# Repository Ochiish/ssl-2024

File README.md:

# 2024 season Ri-one SSL circuit
# Content
- MainBoard
- SubBoard
- raspberry pi shield
- phototransistor
- bldc

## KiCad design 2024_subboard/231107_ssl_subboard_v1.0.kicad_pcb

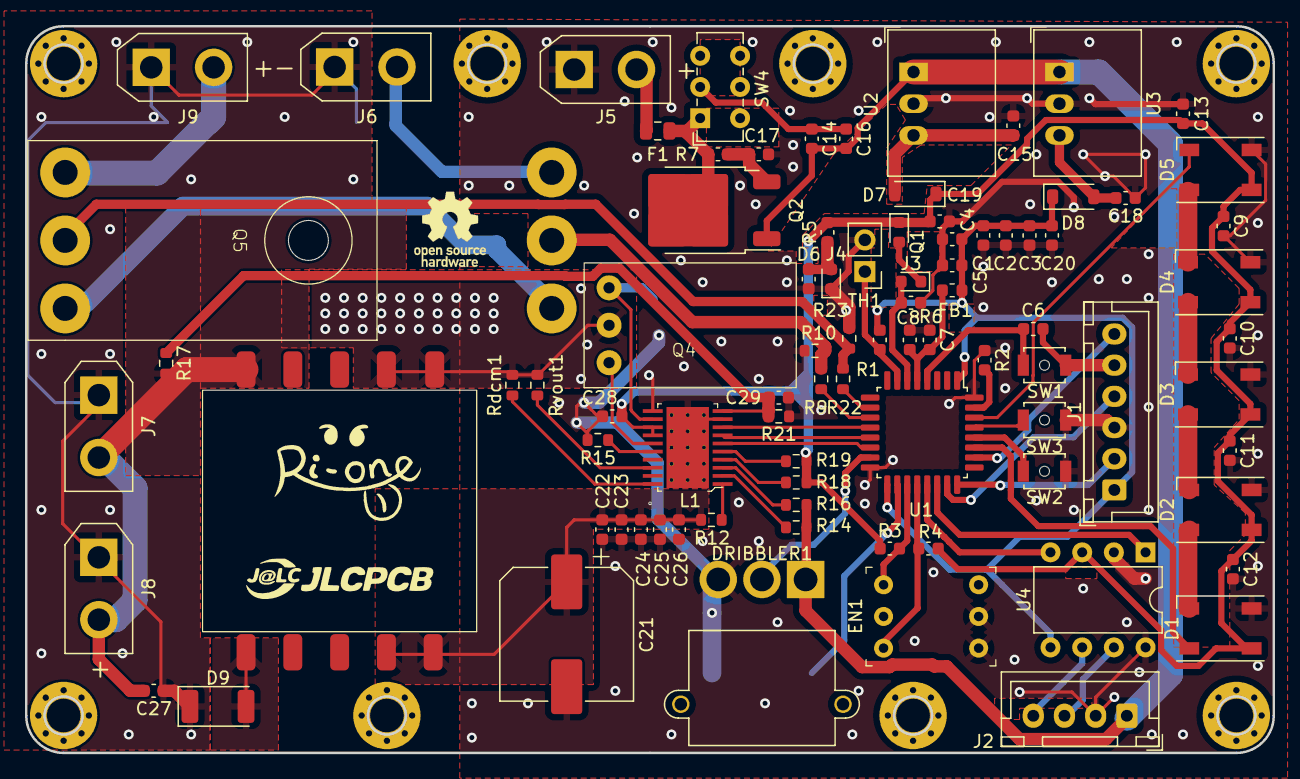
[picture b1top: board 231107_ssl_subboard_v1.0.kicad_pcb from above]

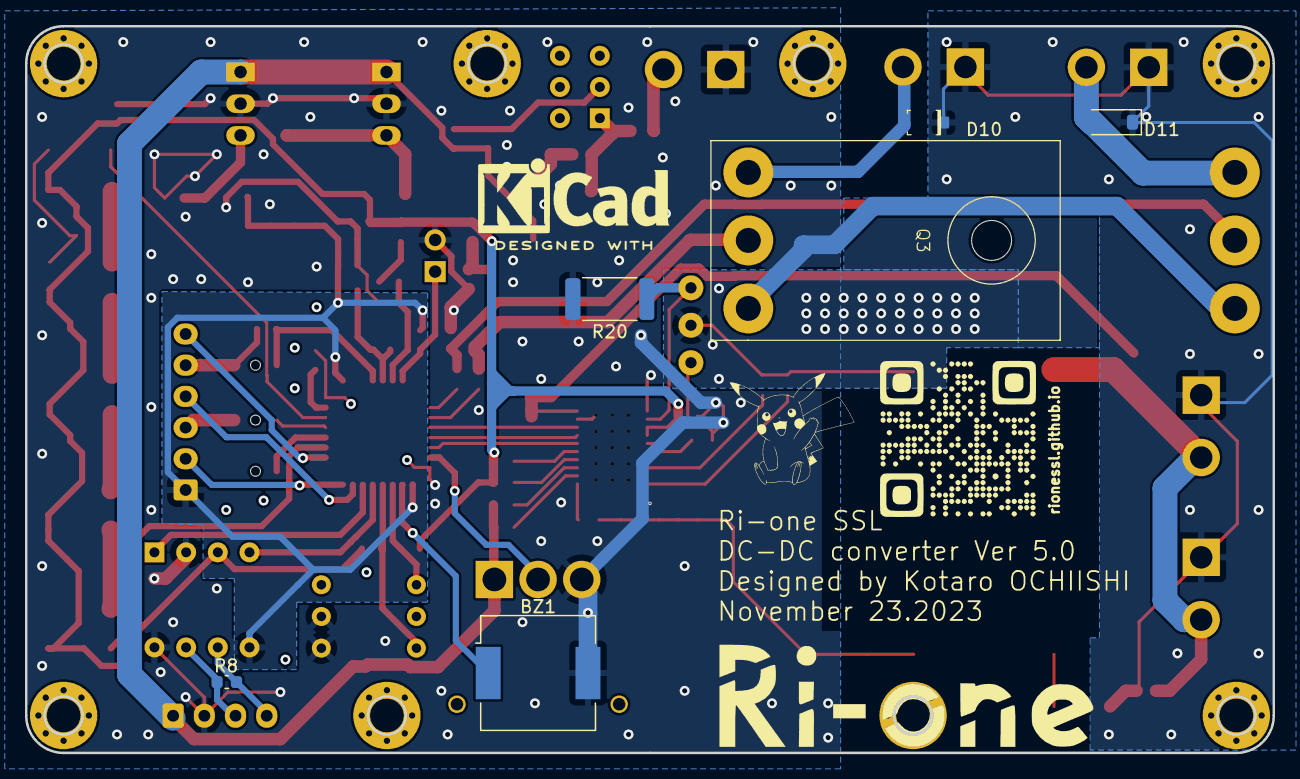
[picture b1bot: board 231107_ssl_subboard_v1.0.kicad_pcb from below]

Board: 2 copper layers, 100.0 x 58.2 mm, 93 parts (6 on the bottom side), 62 nets.

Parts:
BZ1: Buzzer; Buzzer_CUI_CPT-9019S-SMT
C1, C2, C3, C4, C5, C6, C7, C8, C9, C10, C11, C12, C13, C14, C16, C17, C19, C20: 0.1uF; C_0603_1608Metric
C15, C18, C22, C23, C24, C25, C26: 2.2u; C_0603_1608Metric
C21: 680u; CP_Elec_10x10.5
C27: 0.47u; C_0603_1608Metric
C28, C29: 10n; C_0603_1608Metric
D1, D2, D3, D4, D5: ws2812b; LED_Cree-PLCC4_5x5mm_CW
D6: LED; C_0603_1608Metric
D7, D8: SS2040FL; D_SOD-123
D9: 1.5KExxA; D_2010_5025Metric
D10: 1.5KExxA; SOD-123
D11: 1.5KExxA; D_SOD-123
DRIBBLER1: MR30PW-M; AMASS_MR30PW-M_1x03_P3.50mm_Horizontal
EN1: RotaryEncoder_Switch; SOCKET_DIP-6_7.62mm_Conn
F1: Fuse; Fuse_0805_2012Metric
FB1: FerriteBead_Small; L_0603_1608Metric
J1: pc to stm32; JST_XH_B6B-XH-A_1x06_P2.50mm_Vertical
J2: main to sub; JST_XH_B4B-XH-A_1x04_P2.50mm_Vertical
J3: PHOTOCOUPLER; LED_0603_1608Metric
J4: LED; LED_0603_1608Metric
J5: lipo_3cell; AMASS_XT30UPB-M_1x02_P5.0mm_Vertical
J6: s1; AMASS_XT30UPB-F_1x02_P5.0mm_Vertical
J7: c1; AMASS_XT30UPB-F_1x02_P5.0mm_Vertical
J8: c2; AMASS_XT30UPB-F_1x02_P5.0mm_Vertical
J9: s2; AMASS_XT30UPB-F_1x02_P5.0mm_Vertical
L1: TSSOP-20-1EP_W4.4mm
Q1: Q_Photo_NPN; LED_0603_1608Metric
Q2: PMOS; TO-252-2
Q3, Q5: NMOS; IRFP150NPbF
Q4: Q_NMOS_DGS; tk20a60u
R1, R3, R4: 5k; C_0603_1608Metric
R2, R7: 10k; C_0603_1608Metric
R5: 470; C_0603_1608Metric
R6: 20k; C_0603_1608Metric
R8: 120; C_0603_1608Metric
R9, R22: 100; R_0603_1608Metric
R10, R23: 1k; R_0603_1608Metric
R12: 40.2k; R_0603_1608Metric
R14, R18: 69.8k; R_0603_1608Metric
R15: 1.65; R_0603_1608Metric
R16, R19: 475k; R_0603_1608Metric
R17: 124; R_0603_1608Metric
R20: 6m; R_2512_6332Metric
R21: 0.768k; R_0603_1608Metric
Rdcm1: 18.2k; R_0603_1608Metric
Rvout1: 40.2k; R_0603_1608Metric
SW1, SW2, SW3: SW_Push; SW_SPST_B3U-1000P-B
SW4: SW_SPST; SW_E-Switch_EG1271_SPDT
TH1: Thermistor; PinHeader_1x02_P2.54mm_Vertical
U1: STM32F303K8Tx; LQFP-32_7x7mm_P0.8mm
U2: M78AR05-1; Converter_DCDC_RECOM_R-78E-0.5_THT
U3: M78AR033-1; Converter_DCDC_RECOM_R-78E-0.5_THT
U4: MCP2562-E-P; DIP-8_W7.62mm
U5: 32052

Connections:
+3V3: C1.2, C2.2, C3.2, C4.2, C5.2, C20.2, D8.1 (K), FB1.1, J1.1, R1.2, U1.1 (VDD), U1.17 (VDD), U4.5 (Vio)
+5V: C9.1, C10.1, C11.1, C12.1, C13.1, C19.2, C28.1, D1.3 (VDD), D2.3 (VDD), D3.3 (VDD), D4.3 (VDD), D5.3 (VDD), D7.1 (K), L1.13 (VCC), L1.14 (LVGATE), Q1.1 (C), R3.1, R4.1, R5.2, R18.1, R19.1, U4.3 (VDD)
+15V: C14.2, C16.2, DRIBBLER1.1, J2.1, Q2.1 (D), R14.1, R16.1, U2.1 (IN), U3.1 (IN)
+BATT: F1.1, J5.2
CANH: J2.3, R8.2, U4.7 (CANH)
CANL: J2.4, R8.1, U4.6 (CANL)
CANRX: U1.21 (PA11), U4.4 (RXD)
CANTX: U1.22 (PA12), U4.1 (TXD)
CHARGE: L1.8 (CHARGE), U1.12 (PA6)
Cvtrans: C21.1, C22.1, C23.1, C24.1, C25.1, C26.1, R12.1, U5.4 (4IN), U5.5 (5IN)
DCDC_OUT: C27.1, D9.1 (A1), D10.1 (A1), D11.1 (A1), J6.1, J7.1, J8.1, J9.1
DIN: D1.4 (DIN), U1.27 (PB4)
DONE: L1.7 (DONE), U1.13 (PA7)
DOUT: D5.1 (DOUT), U1.30 (PB7)
DR_PWM: DRIBBLER1.2, U1.15 (PB1)
DR_SW: SW3.2, U1.29 (PB6)
Drain: Q4.1 (D), Rdcm1.2, Rvout1.2, U5.6 (6IN), U5.7 (7IN)
ENCODER_A: EN1.1 (A), R3.2, U1.19 (PA9)
ENCODER_B: EN1.3 (B), R4.2, U1.20 (PA10)
FAULT: L1.6 (FAULT), U1.14 (PB0)
GND: BZ1.2 (+), C1.1, C2.1, C3.1, C4.1, C5.1, C7.1, C8.1, C9.2, C10.2, C11.2, C12.2, C13.2, C15.1, C17.1, C18.1, C19.1, C20.1, C21.2, C22.2, C23.2, C24.2, C25.2, C26.2, C28.2, C29.2, D1.2 (GND), D2.2 (GND), D3.2 (GND), D4.2 (GND), D5.2 (GND), D6.1 (K), DRIBBLER1.3, EN1.4 (S1), EN1.5 (S2), J1.3, J2.2, J4.1, J5.1, L1.9 (CLAMP), L1.11 (CSN), L1.21 (GND), Q3.3 (S), Q5.3 (S), R2.1, R6.2, R10.1, R15.2, R20.2, R21.1, R23.1, SW2.1, SW3.1, TH1.2, U1.16 (VSS), U1.32 (VSS), U2.2 (GND), U3.2 (GND), U4.2 (VSS), U4.8 (STBY)
KICK_SW: SW2.2, U1.28 (PB5)
NRST: C6.1, J1.5, SW1.1
unnamed: BZ1.1 (-), U1.18 (PA8)
unnamed: D1.1 (DOUT), D2.4 (DIN)
unnamed: D2.1 (DOUT), D3.4 (DIN)
unnamed: D3.1 (DOUT), D4.4 (DIN)
unnamed: D4.1 (DOUT), D5.4 (DIN)
unnamed: D6.2 (A), J4.2, R5.1
unnamed: C15.2, D7.2 (A), U2.3 (OUT)
unnamed: C18.2, D8.2 (A), U3.3 (OUT)
unnamed: D10.2 (A2), J6.2, Q3.1 (D)
unnamed: D11.2 (A2), J9.2, Q5.1 (D)
unnamed: J3.1, Q1.2 (E)
unnamed: L1.12 (CSP), Q4.3 (S), R20.1
unnamed: C29.1, L1.10 (FB), R17.1, R21.2
unnamed: L1.15 (HVGATE), Q4.2 (G)
unnamed: L1.3 (OVLO1), R16.2
unnamed: L1.5 (OVLO2), R19.2
unnamed: L1.16 (RBG), R15.1
unnamed: L1.20 (RDCM), Rdcm1.1
unnamed: L1.18 (RVOUT), Rvout1.1
unnamed: L1.1 (RVTRANS), R12.2
unnamed: L1.2 (UVLO1), R14.2
unnamed: L1.4 (UVLO2), R18.2
unnamed: F1.2, Q2.2 (G), R7.2, SW4.1 (A)
unnamed: C17.2, Q2.3 (S), R7.1
unnamed: Q3.2 (G), R9.2, R10.2
unnamed: Q5.2 (G), R22.2, R23.2
unnamed: C14.1, C16.1, SW4.2 (B)
unnamed: R2.2, U1.31 (BOOT0)
unnamed: C6.2, SW1.2, U1.4 (NRST)
unnamed: R1.1, TH1.1, U1.7 (PA1)
unnamed: C7.2, C8.2, FB1.2, U1.5 (VDDA)
STRAIGHT: R9.1, U1.11 (PA5)
SYS-SWCLK: J1.2, U1.24 (PA14)
SYS-SWDIO: J1.4, U1.23 (PA13)
SYS-SWO: J1.6, U1.26 (PB3)
TR_SIG: J3.2, R6.1, U1.6 (PA0)
Vout: D9.2 (A2), U5.1 (1OUT)
tip: R22.1, U1.10 (PA4)
trans2: C27.2, J7.2, J8.2, R17.2, U5.10 (10OUT)

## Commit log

2023-11-29 second commit
2023-11-29 Add .gitignore file
2023-11-29 remove
2023-11-29 add image
2023-11-29 README.md の更新
